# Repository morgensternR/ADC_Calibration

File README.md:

# ADC_Calibration
Collection/file history in making the ADC calibration board

 Copyright 2023 Ryan Morgenstern

   Licensed under the Apache License, Version 2.0 (the "License");
   you may not use this file except in compliance with the License.
   You may obtain a copy of the License at

       http://www.apache.org/licenses/LICENSE-2.0

   Unless required by applicable law or agreed to in writing, software
   distributed under the License is distributed on an "AS IS" BASIS,
   WITHOUT WARRANTIES OR CONDITIONS OF ANY KIND, either express or implied.
   See the License for the specific language governing permissions and
   limitations under the License.

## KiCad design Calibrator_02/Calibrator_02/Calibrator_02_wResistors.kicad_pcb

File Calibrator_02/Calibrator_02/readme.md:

Copyright 2023 Ryan Morgenstern

   Licensed under the Apache License, Version 2.0 (the "License");
   you may not use this file except in compliance with the License.
   You may obtain a copy of the License at

       http://www.apache.org/licenses/LICENSE-2.0

   Unless required by applicable law or agreed to in writing, software
   distributed under the License is distributed on an "AS IS" BASIS,
   WITHOUT WARRANTIES OR CONDITIONS OF ANY KIND, either express or implied.
   See the License for the specific language governing permissions and
   limitations under the License.

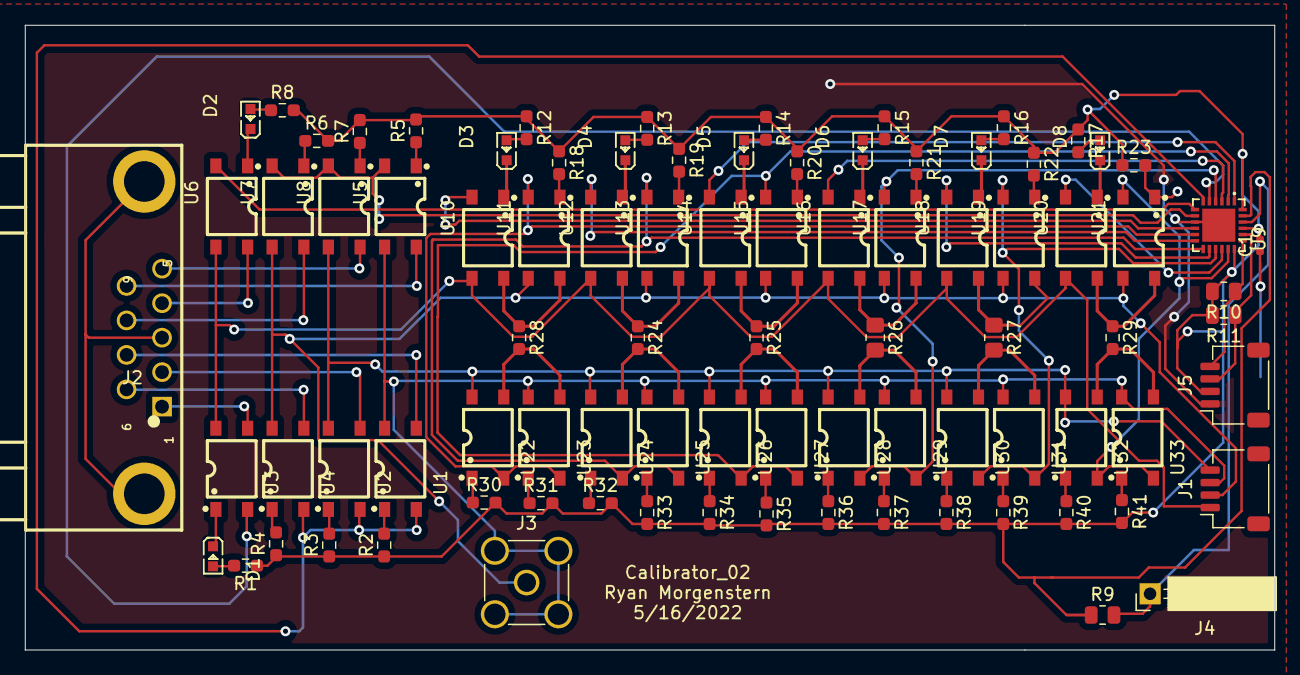
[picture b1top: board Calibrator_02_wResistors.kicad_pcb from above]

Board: 2 copper layers, 100.0 x 50.0 mm, 88 parts (0 on the bottom side), 86 nets.

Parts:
C1: 100nF; C_0402_1005Metric
D1, D2, D3, D4, D5, D6, D7, D8: LED; LED0603-RD
J1, J5: Conn_01x04; JST_SH_SM04B-SRSS-TB_1x04-1MP_P1.00mm_Horizontal
J2: DB9_Female_MountingHoles; DSUB-TH_DMR-9S
J3: Conn_Coaxial; SMA_Amphenol_901-144_Vertical
J4: Conn_01x01_Female; PinSocket_1x01_P2.54mm_Horizontal
R1, R8, R12, R13, R14, R15, R16, R17: 95.3 1%; R_0603_1608Metric_Pad0.98x0.95mm_HandSolder
R2, R3, R4, R5, R6, R7, R18, R19, R20, R21, R22, R23, R30, R31, R32, R33, R34, R35, R36, R37, R38, R39, R40, R41: 84.5 1%; R_0603_1608Metric_Pad0.98x0.95mm_HandSolder
R9, R10, R11: 4.7K; R_0805_2012Metric
R24: 120K_0.1%; R_0603_1608Metric_Pad0.98x0.95mm_HandSolder
R25: 140K_0.1%; R_0603_1608Metric_Pad0.98x0.95mm_HandSolder
R26: 160K_0.1%; R_0805_2012Metric_Pad1.20x1.40mm_HandSolder
R27: 180K_0.1%; R_0805_2012Metric_Pad1.20x1.40mm_HandSolder
R28: 100K_0.1%; R_0603_1608Metric_Pad0.98x0.95mm_HandSolder
R29: 200K_0.1%; R_0603_1608Metric_Pad0.98x0.95mm_HandSolder
U1, U2, U3, U4, U5, U6, U7, U8, U10, U11, U12, U13, U14, U15, U16, U17, U18, U19, U20, U21, U22, U23, U24, U25, U26, U27, U28, U29, U30, U31, U32, U33: KAQY214STLD; SOP-4_L3.9-W4.4-P2.54-LS7.0-BR
U9: AW9523BTQR; TQFN-24_L4.0-W4.0-P0.50-TL-EP

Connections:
+3V3: C1.2, J5.2, R1.1, R2.1, R3.1, R4.1, R5.2, R6.2, R7.2, R8.2, R9.1, R10.2, R11.2, R12.1, R13.1, R14.1, R15.1, R16.1, R17.1, R18.1, R19.1, R20.1, R21.1, R22.1, R23.1, R30.2, R31.2, R32.2, R33.2, R34.2, R35.2, R36.2, R37.2, R38.2, R39.2, R40.2, R41.2, U9.18, U9.21, U9.23, U9.24
/I+: J2.1, U3.3
/I-: J2.2, U2.3
/I_00: U3.2, U9.5
/I_01: U1.2, U2.2, U4.2, U9.6
/I_02: U6.2, U9.7
/I_2+: J2.4, U6.4
/I_2-: J2.5, U8.4
/I_03: U5.2, U7.2, U8.2, U9.8
/I_04: U9.10, U10.2
/I_05: U9.11, U11.2, U22.2, U23.2
/I_06: U9.12, U12.2
/I_07: U9.13, U13.2, U24.2, U25.2
/I_10: U9.1, U14.2
/I_11: U9.2, U15.2, U26.2, U27.2
/I_12: U9.3, U16.2
/I_13: U9.4, U17.2, U28.2, U29.2
/I_14: U9.14, U18.2
/I_15: U9.15, U19.2, U30.2, U31.2
/I_16: U9.16, U20.2
/I_17: U9.17, U21.2, U32.2, U33.2
/Resistor_Network/I+: J1.1, U3.4, U6.3, U10.3, U12.3, U14.3, U16.3, U18.3, U20.3
/Resistor_Network/I-: J1.4, U2.4, U8.3, U22.4, U24.4, U26.4, U28.4, U30.4, U32.4
/Resistor_Network/V+: J1.2, J3.1, U4.4, U7.3, U11.3, U13.3, U15.3, U17.3, U19.3, U21.3
/Resistor_Network/V-: J1.3, J3.2, U1.4, U5.3, U23.4, U25.4, U27.4, U29.4, U31.4, U33.4
/V+: J2.6, U4.3
/V-: J2.7, U1.3
/V_2+: J2.8, U7.4
/V_2-: J2.9, U5.4
GND: C1.1, J5.1, U9.9, U9.25
GNDS: J2.0, J2.3
unnamed: D1.1, U3.1
unnamed: D1.2, R1.2
unnamed: D2.1, U6.1
unnamed: D2.2, R8.1
unnamed: D3.1, U10.1
unnamed: D3.2, R12.2
unnamed: D4.1, U12.1
unnamed: D4.2, R13.2
unnamed: D5.1, U14.1
unnamed: D5.2, R14.2
unnamed: D6.1, U16.1
unnamed: D6.2, R15.2
unnamed: D7.1, U18.1
unnamed: D7.2, R16.2
unnamed: D8.1, U20.1
unnamed: D8.2, R17.2
unnamed: J4.1, R9.2, U9.22
unnamed: J5.3, R11.1, U9.20
unnamed: J5.4, R10.1, U9.19
unnamed: R2.2, U1.1
unnamed: R3.2, U2.1
unnamed: R4.2, U4.1
unnamed: R5.1, U5.1
unnamed: R6.1, U7.1
unnamed: R7.1, U8.1
unnamed: R18.2, U11.1
unnamed: R19.2, U13.1
unnamed: R20.2, U15.1
unnamed: R21.2, U17.1
unnamed: R22.2, U19.1
unnamed: R23.2, U21.1
unnamed: R24.1, U12.4, U13.4
unnamed: R24.2, U24.3, U25.3
unnamed: R25.1, U14.4, U15.4
unnamed: R25.2, U26.3, U27.3
unnamed: R26.1, U16.4, U17.4
unnamed: R26.2, U28.3, U29.3
unnamed: R27.1, U18.4, U19.4
unnamed: R27.2, U30.3, U31.3
unnamed: R28.1, U10.4, U11.4
unnamed: R28.2, U22.3, U23.3
unnamed: R29.1, U20.4, U21.4
unnamed: R29.2, U32.3, U33.3
unnamed: R30.1, U22.1
unnamed: R31.1, U23.1
unnamed: R32.1, U24.1
unnamed: R33.1, U25.1
unnamed: R34.1, U26.1
unnamed: R35.1, U27.1
unnamed: R36.1, U28.1
unnamed: R37.1, U29.1
unnamed: R38.1, U30.1
unnamed: R39.1, U31.1
unnamed: R40.1, U32.1
unnamed: R41.1, U33.1

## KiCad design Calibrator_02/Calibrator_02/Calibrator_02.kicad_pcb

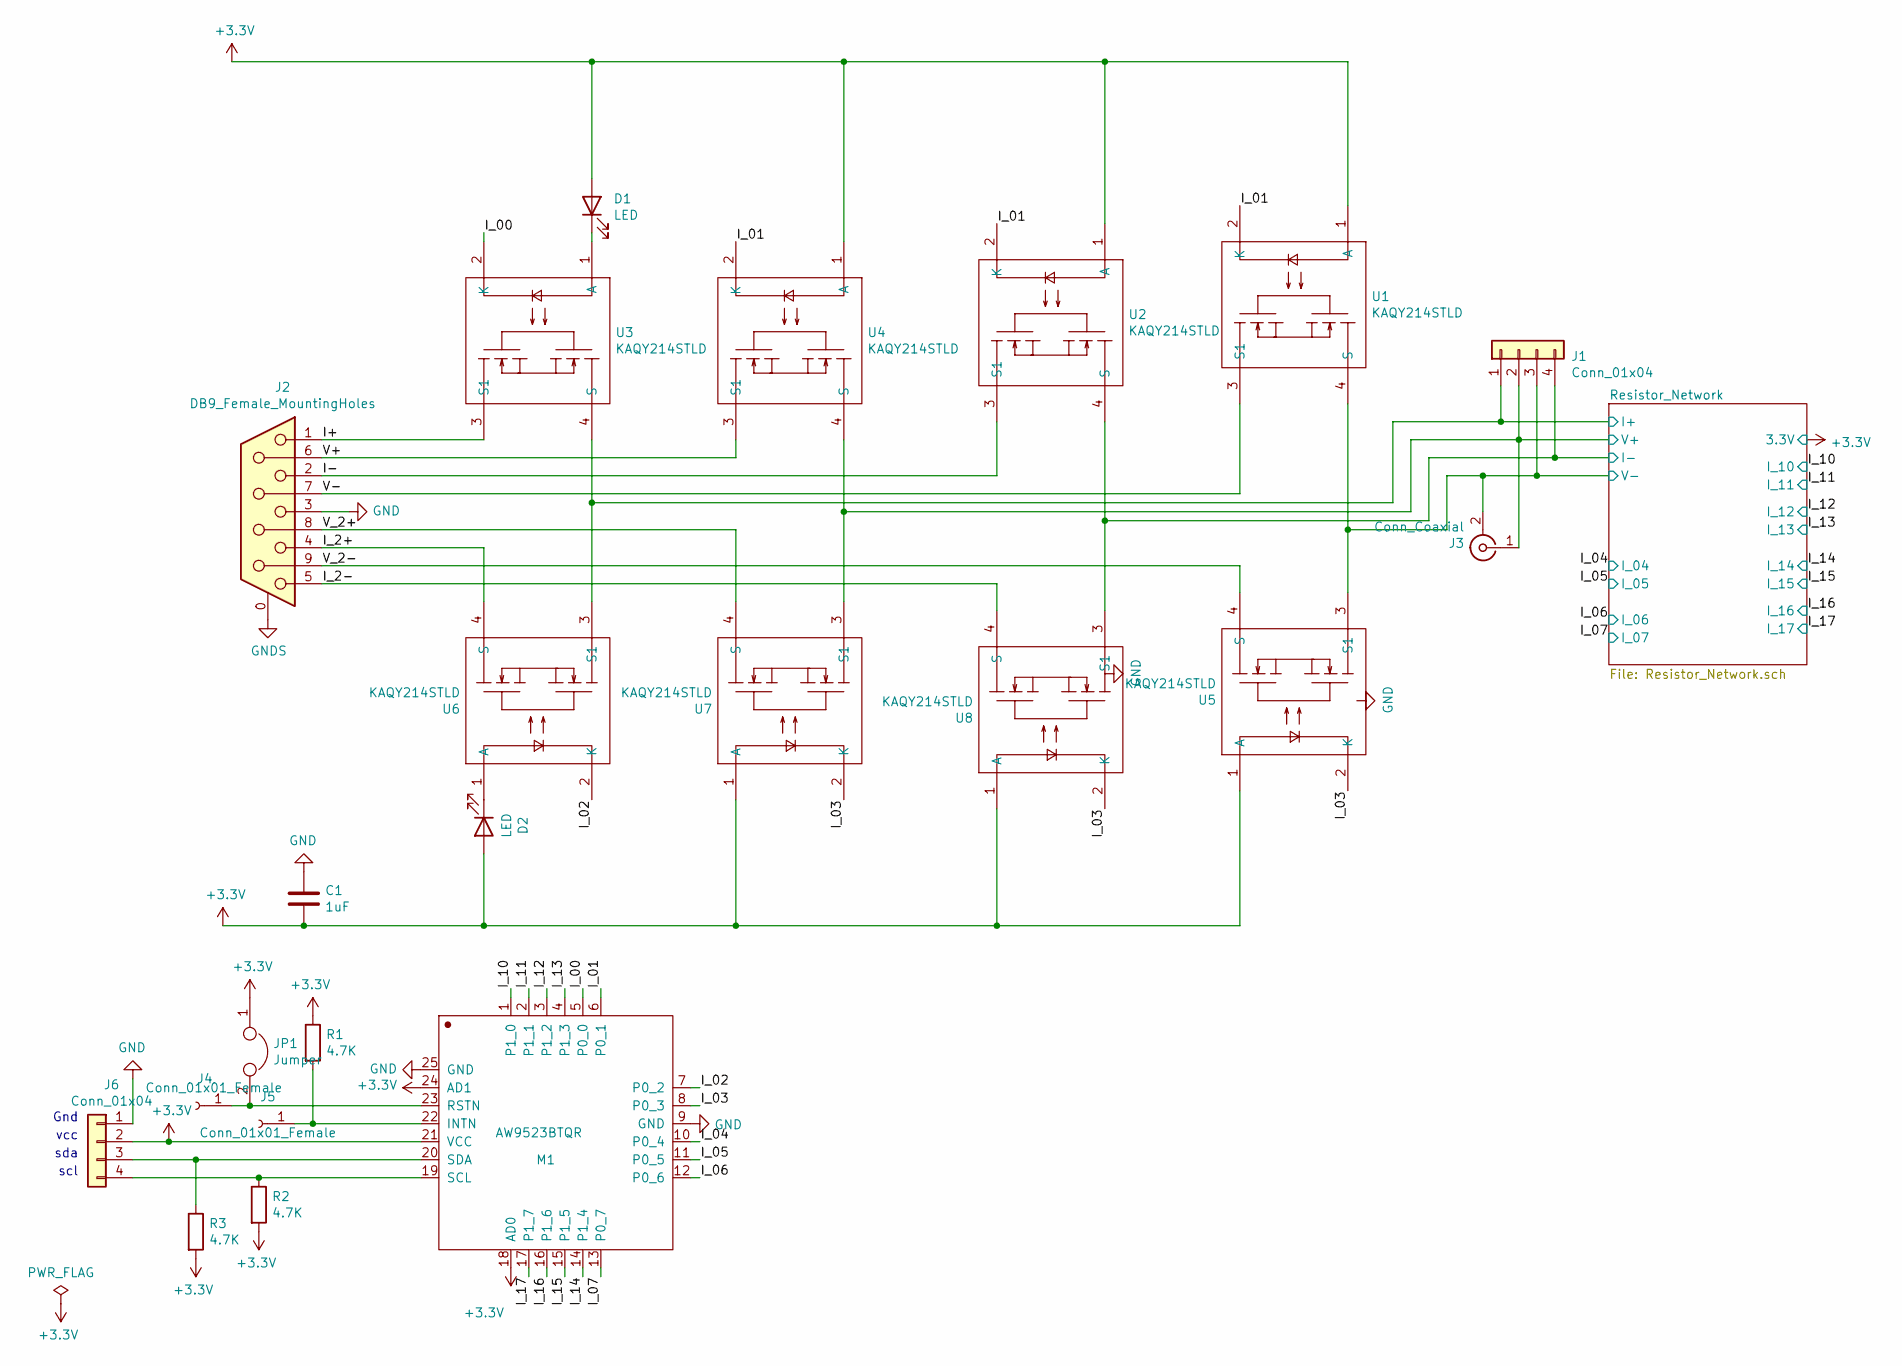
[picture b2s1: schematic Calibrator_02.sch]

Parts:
C1: 1uF; C_0402_1005Metric; LCSC C77009
D1, D2: LED; LED0603-RD; LCSC C125093
J1, J6: Conn_01x04; JST_SH_SM04B-SRSS-TB_1x04-1MP_P1.00mm_Horizontal; LCSC C371571
J2: DB9_Female_MountingHoles; DSUB-TH_DMR-9S; LCSC C141882
J3: Conn_Coaxial; SMA_Amphenol_901-144_Vertical
J4, J5: Conn_01x01_Female; PinSocket_1x01_P2.54mm_Horizontal
JP1: Jumper; SolderJumper-2_P1.3mm_Open_RoundedPad1.0x1.5mm
M1: AW9523BTQR; TQFN-24_L4.0-W4.0-P0.50-TL-EP; LCSC C148077
R1, R2, R3: 4.7K; R_0805_2012Metric; LCSC C17673
U1, U2, U3, U4, U5, U6, U7, U8: KAQY214STLD; SOP-4_L3.9-W4.4-P2.54-LS7.0-BR; LCSC C113331

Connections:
/I+: J2.1, U3.3 (S1)
/I-: J2.2, U2.3 (S1)
/I_00: M1.5 (P0_0), U3.2 (K)
/I_01: M1.6 (P0_1), U1.2 (K), U2.2 (K), U4.2 (K)
/I_02: M1.7 (P0_2), U6.2 (K)
/I_2+: J2.4, U6.4 (S)
/I_2-: J2.5, U8.4 (S)
/I_03: M1.8 (P0_3), U5.2 (K), U7.2 (K), U8.2 (K)
/I_04: M1.10 (P0_4); also elsewhere on the board
/I_05: M1.11 (P0_5); also elsewhere on the board
/I_06: M1.12 (P0_6); also elsewhere on the board
/I_07: M1.13 (P0_7); also elsewhere on the board
/I_10: M1.1 (P1_0); also elsewhere on the board
/I_11: M1.2 (P1_1); also elsewhere on the board
/I_12: M1.3 (P1_2); also elsewhere on the board
/I_13: M1.4 (P1_3); also elsewhere on the board
/I_14: M1.14 (P1_4); also elsewhere on the board
/I_15: M1.15 (P1_5); also elsewhere on the board
/I_16: M1.16 (P1_6); also elsewhere on the board
/I_17: M1.17 (P1_7); also elsewhere on the board
/Resistor_Network/I+: J1.1, U3.4 (S), U6.3 (S1); also elsewhere on the board
/Resistor_Network/I-: J1.4, U2.4 (S), U8.3 (S1); also elsewhere on the board
/Resistor_Network/V+: J1.2, J3.1 (In), U4.4 (S), U7.3 (S1); also elsewhere on the board
/Resistor_Network/V-: J1.3, J3.2 (Ext), U1.4 (S), U5.3 (S1); also elsewhere on the board
/V+: J2.6, U4.3 (S1)
/V-: J2.7, U1.3 (S1)
/V_2+: J2.8, U7.4 (S)
/V_2-: J2.9, U5.4 (S)
GND: C1.1, J2.3, J6.1, M1.9 (GND), M1.25 (GND)
GNDS: J2.0 (PAD)
unnamed: D1.1 (K), U3.1 (A)
unnamed: D2.1 (K), U6.1 (A)
unnamed: J5.1, M1.22 (INTN), R1.2
unnamed: J6.3, M1.20 (SDA), R3.1
unnamed: J6.4, M1.19 (SCL), R2.1

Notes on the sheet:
Gnd
vcc
sda
scl

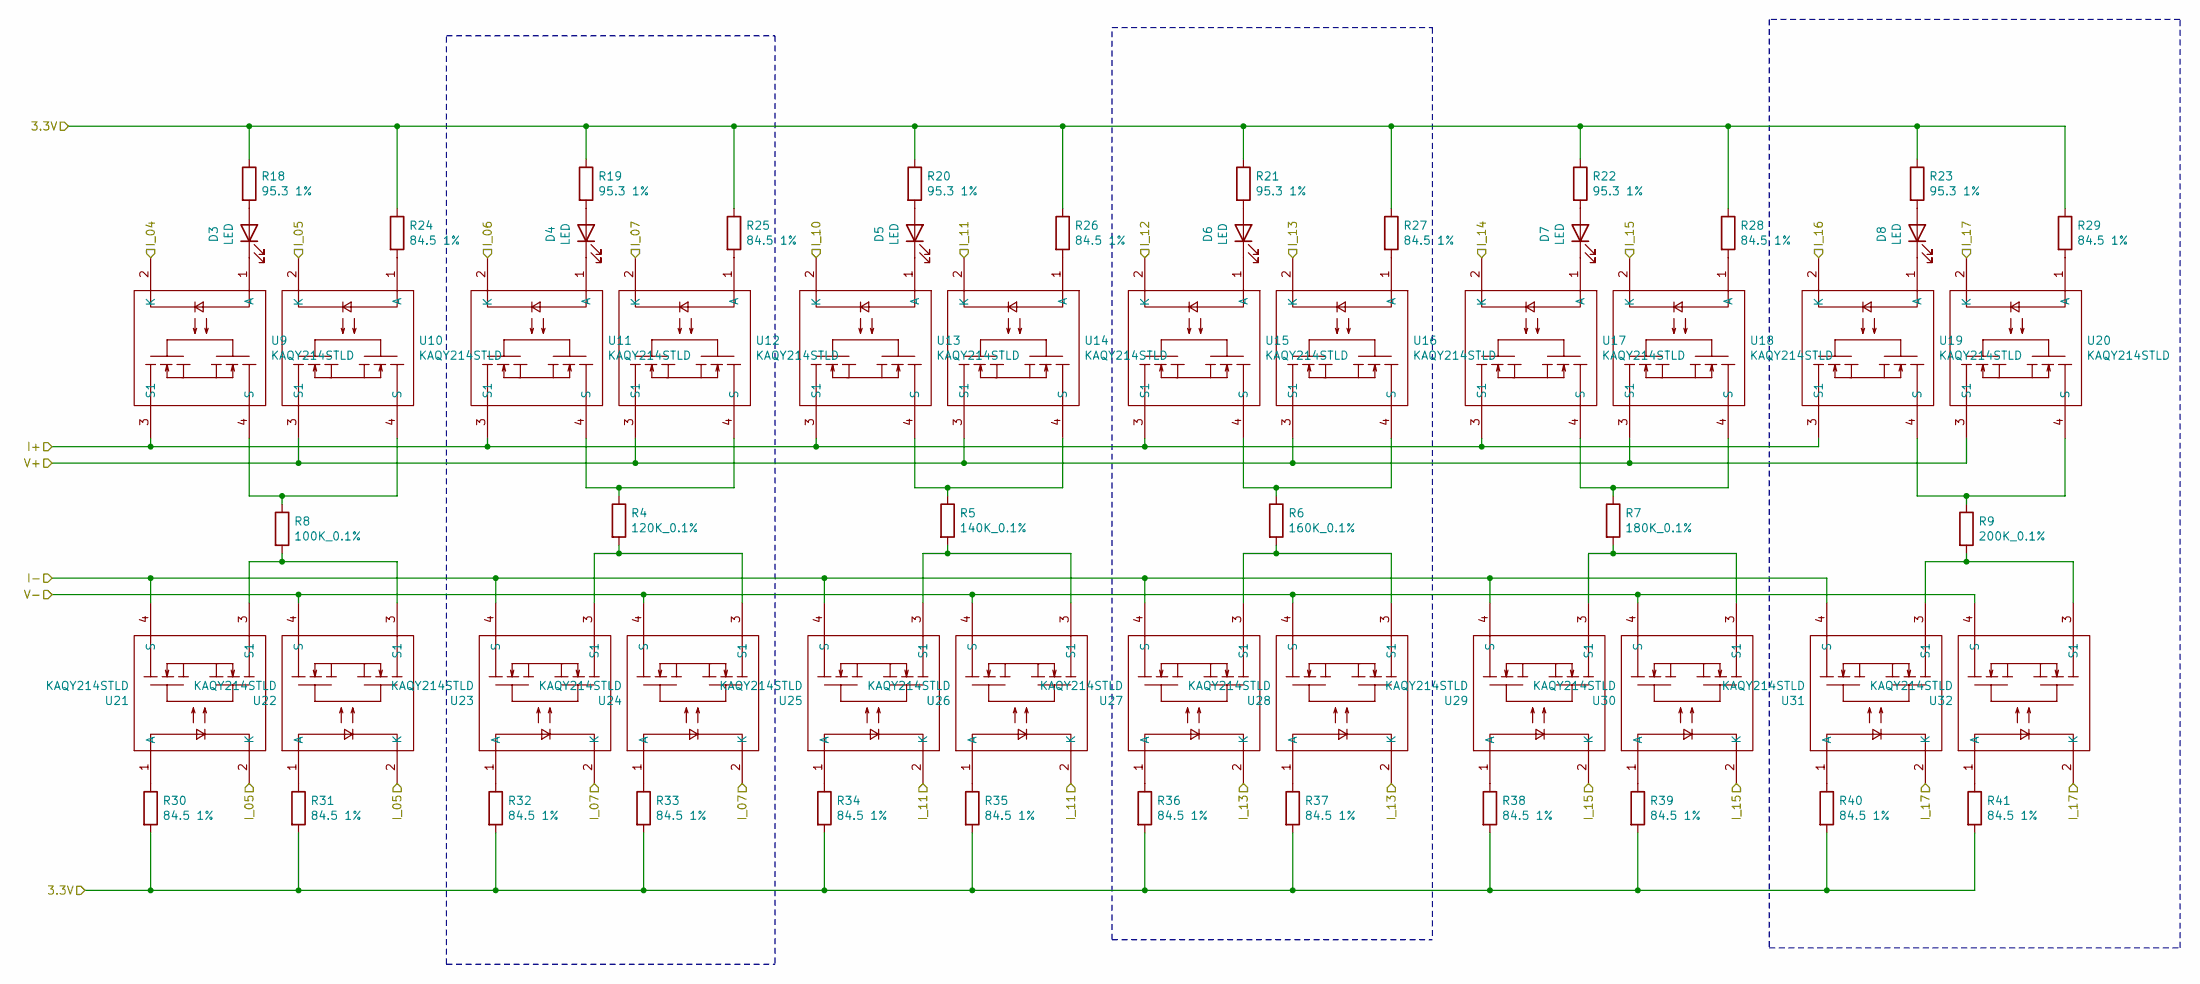
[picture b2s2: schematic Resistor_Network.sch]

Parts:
D3, D4, D5, D6, D7, D8: LED; LED0603-RD; LCSC C125093
R4: 120K_0.1%; R_0603_1608Metric_Pad0.98x0.95mm_HandSolder; LCSC C136959
R5: 140K_0.1%; R_0603_1608Metric_Pad0.98x0.95mm_HandSolder; LCSC C326761
R6: 160K_0.1%; R_0805_2012Metric_Pad1.20x1.40mm_HandSolder; LCSC C473318
R7: 180K_0.1%; R_0805_2012Metric_Pad1.20x1.40mm_HandSolder; LCSC C473319
R8: 100K_0.1%; R_0603_1608Metric_Pad0.98x0.95mm_HandSolder; LCSC C335088
R9: 200K_0.1%; R_0603_1608Metric_Pad0.98x0.95mm_HandSolder; LCSC C394540
R18, R19, R20, R21, R22, R23: 95.3 1%; R_0603_1608Metric_Pad0.98x0.95mm_HandSolder; LCSC C218188
R24, R25, R26, R27, R28, R29, R30, R31, R32, R33, R34, R35, R36, R37, R38, R39, R40, R41: 84.5 1%; R_0603_1608Metric_Pad0.98x0.95mm_HandSolder; LCSC C177824
U9, U10, U11, U12, U13, U14, U15, U16, U17, U18, U19, U20, U21, U22, U23, U24, U25, U26, U27, U28, U29, U30, U31, U32: KAQY214STLD; SOP-4_L3.9-W4.4-P2.54-LS7.0-BR; LCSC C113331

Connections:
/I_04: U9.2 (K); also elsewhere on the board
/I_05: U10.2 (K), U21.2 (K), U22.2 (K); also elsewhere on the board
/I_06: U11.2 (K); also elsewhere on the board
/I_07: U12.2 (K), U23.2 (K), U24.2 (K); also elsewhere on the board
/I_10: U13.2 (K); also elsewhere on the board
/I_11: U14.2 (K), U25.2 (K), U26.2 (K); also elsewhere on the board
/I_12: U15.2 (K); also elsewhere on the board
/I_13: U16.2 (K), U27.2 (K), U28.2 (K); also elsewhere on the board
/I_14: U17.2 (K); also elsewhere on the board
/I_15: U18.2 (K), U29.2 (K), U30.2 (K); also elsewhere on the board
/I_16: U19.2 (K); also elsewhere on the board
/I_17: U20.2 (K), U31.2 (K), U32.2 (K); also elsewhere on the board
/Resistor_Network/I+: U9.3 (S1), U11.3 (S1), U13.3 (S1), U15.3 (S1), U17.3 (S1), U19.3 (S1); also elsewhere on the board
/Resistor_Network/I-: U21.4 (S), U23.4 (S), U25.4 (S), U27.4 (S), U29.4 (S), U31.4 (S); also elsewhere on the board
/Resistor_Network/V+: U10.3 (S1), U12.3 (S1), U14.3 (S1), U16.3 (S1), U18.3 (S1), U20.3 (S1); also elsewhere on the board
/Resistor_Network/V-: U22.4 (S), U24.4 (S), U26.4 (S), U28.4 (S), U30.4 (S), U32.4 (S); also elsewhere on the board
unnamed: D3.1 (K), U9.1 (A)
unnamed: D3.2 (A), R18.2
unnamed: D4.1 (K), U11.1 (A)
unnamed: D4.2 (A), R19.2
unnamed: D5.1 (K), U13.1 (A)
unnamed: D5.2 (A), R20.2
unnamed: D6.1 (K), U15.1 (A)
unnamed: D6.2 (A), R21.2
unnamed: D7.1 (K), U17.1 (A)
unnamed: D7.2 (A), R22.2
unnamed: D8.1 (K), U19.1 (A)
unnamed: D8.2 (A), R23.2
unnamed: R4.1, U11.4 (S), U12.4 (S)
unnamed: R4.2, U23.3 (S1), U24.3 (S1)
unnamed: R5.1, U13.4 (S), U14.4 (S)
unnamed: R5.2, U25.3 (S1), U26.3 (S1)
unnamed: R6.1, U15.4 (S), U16.4 (S)
unnamed: R6.2, U27.3 (S1), U28.3 (S1)
unnamed: R7.1, U17.4 (S), U18.4 (S)
unnamed: R7.2, U29.3 (S1), U30.3 (S1)
unnamed: R8.1, U9.4 (S), U10.4 (S)
unnamed: R8.2, U21.3 (S1), U22.3 (S1)
unnamed: R9.1, U19.4 (S), U20.4 (S)
unnamed: R9.2, U31.3 (S1), U32.3 (S1)
unnamed: R24.2, U10.1 (A)
unnamed: R25.2, U12.1 (A)
unnamed: R26.2, U14.1 (A)
unnamed: R27.2, U16.1 (A)
unnamed: R28.2, U18.1 (A)
unnamed: R29.2, U20.1 (A)
unnamed: R30.1, U21.1 (A)
unnamed: R31.1, U22.1 (A)
unnamed: R32.1, U23.1 (A)
unnamed: R33.1, U24.1 (A)
unnamed: R34.1, U25.1 (A)
unnamed: R35.1, U26.1 (A)
unnamed: R36.1, U27.1 (A)
unnamed: R37.1, U28.1 (A)
unnamed: R38.1, U29.1 (A)
unnamed: R39.1, U30.1 (A)
unnamed: R40.1, U31.1 (A)
unnamed: R41.1, U32.1 (A)

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
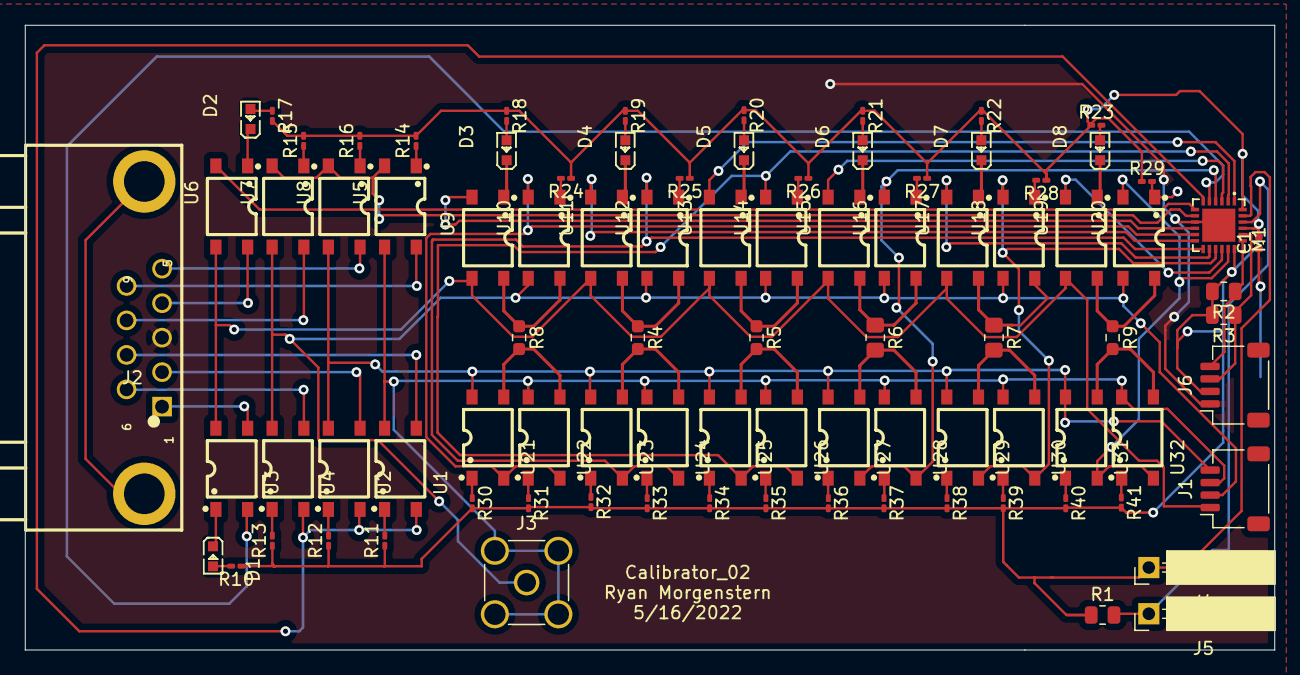
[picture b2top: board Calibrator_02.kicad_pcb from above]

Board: 2 copper layers, 100.0 x 50.0 mm, 89 parts (0 on the bottom side), 85 nets.

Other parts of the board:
R10, R17: 95.3 1%; R_0201_0603Metric_Pad0.64x0.40mm_HandSolder
R11, R12, R13, R14, R15, R16: 84.5 1%; R_0201_0603Metric_Pad0.64x0.40mm_HandSolder

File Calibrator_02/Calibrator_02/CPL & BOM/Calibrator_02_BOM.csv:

Comment,Designator,Footprint,LCSC
"1uF","C1","Capacitor_SMD:C_0402_1005Metric","C77009"
"LED","D1,D2,D3,D4,D5,D6,D7,D8","0_Resistor_02:LED0603-RD","C125093"
"Conn_01x04","J1,J6","Connector_JST:JST_SH_SM04B-SRSS-TB_1x04-1MP_P1.00mm_Horizontal","C371571"
"DB9_Female_MountingHoles","J2","0_Resistor_02:DSUB-TH_DMR-9S","C141882"
"Conn_Coaxial","J3","Connector_Coaxial:SMA_Amphenol_901-144_Vertical",""
"Conn_01x01_Female","J5","Connector_PinSocket_2.54mm:PinSocket_1x01_P2.54mm_Horizontal",""
"Jumper","JP1","Jumper:SolderJumper-2_P1.3mm_Open_RoundedPad1.0x1.5mm",""
"AW9523BTQR","M1","0_Resistor_02:TQFN-24_L4.0-W4.0-P0.50-TL-EP","C148077"
"4.7K","R1,R2,R3","Resistor_SMD:R_0805_2012Metric","C17673"
"95.3 1%","R10,R17,R18,R19,R20,R21,R22,R23","Resistor_SMD:R_0201_0603Metric_Pad0.64x0.40mm_HandSolder","C218188"
"84.5 1%","R11,R12,R13,R14,R15,R16,R24,R25,R26,R27,R28,R29,R30,R31,R32,R33,R34,R35,R36,R37,R38,R39,R40,R41","Resistor_SMD:R_0201_0603Metric_Pad0.64x0.40mm_HandSolder","C177824"
"120K_0.1%","R4","Resistor_SMD:R_0603_1608Metric_Pad0.98x0.95mm_HandSolder","C136959"
"140K_0.1%","R5","Resistor_SMD:R_0603_1608Metric_Pad0.98x0.95mm_HandSolder","C326761"
"160K_0.1%","R6","Resistor_SMD:R_0805_2012Metric_Pad1.20x1.40mm_HandSolder","C473318"
"180K_0.1%","R7","Resistor_SMD:R_0805_2012Metric_Pad1.20x1.40mm_HandSolder","C473319"
"100K_0.1%","R8","Resistor_SMD:R_0603_1608Metric_Pad0.98x0.95mm_HandSolder","C335088"
"200K_0.1%","R9","Resistor_SMD:R_0603_1608Metric_Pad0.98x0.95mm_HandSolder","C394540"
"KAQY214STLD","U1,U2,U3,U4,U5,U6,U7,U8,U9,U10,U11,U12,U13,U14,U15,U16,U17,U18,U19,U20,U21,U22,U23,U24,U25,U26,U27,U28,U29,U30,U31,U32","0_Resistor_02:SOP-4_L3.9-W4.4-P2.54-LS7.0-BR","C113331"

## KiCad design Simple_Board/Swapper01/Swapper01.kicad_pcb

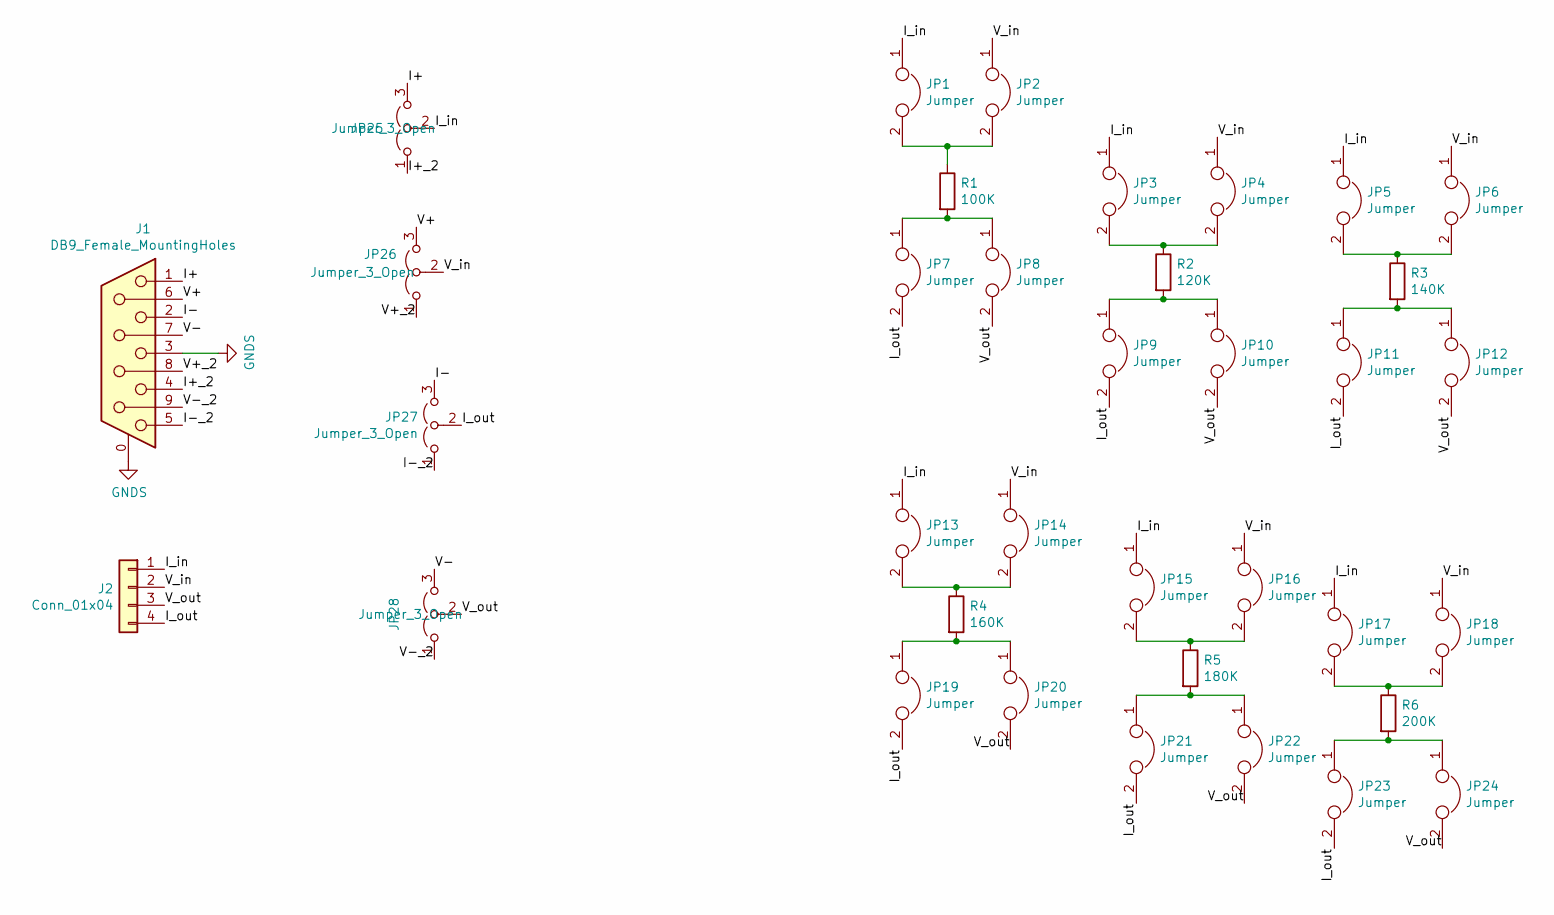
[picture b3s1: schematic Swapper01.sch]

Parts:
J1: DB9_Female_MountingHoles; DSUB-TH_DMR-9S; LCSC C141882
J2: Conn_01x04; JST_SH_SM04B-SRSS-TB_1x04-1MP_P1.00mm_Horizontal
JP1, JP2, JP3, JP4, JP5, JP6, JP7, JP8, JP9, JP10, JP11, JP12, JP13, JP14, JP15, JP16, JP17, JP18, JP19, JP20, JP21, JP22, JP23, JP24: Jumper; SolderJumper-2_P1.3mm_Open_RoundedPad1.0x1.5mm
JP25, JP26, JP27, JP28: Jumper_3_Open; SolderJumper-3_P1.3mm_Open_Pad1.0x1.5mm
R1: 100K; R_0603_1608Metric_Pad0.98x0.95mm_HandSolder; LCSC C335088
R2: 120K; R_0603_1608Metric_Pad0.98x0.95mm_HandSolder; LCSC C136959
R3: 140K; R_0603_1608Metric_Pad0.98x0.95mm_HandSolder; LCSC C326761
R4: 160K; R_0805_2012Metric_Pad1.20x1.40mm_HandSolder; LCSC C473318
R5: 180K; R_0805_2012Metric_Pad1.20x1.40mm_HandSolder; LCSC C473319
R6: 200K; R_0603_1608Metric_Pad0.98x0.95mm_HandSolder; LCSC C394540

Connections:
/I+: J1.1, JP25.3 (B)
/I+_2: J1.4, JP25.1 (A)
/I-: J1.2, JP27.3 (B)
/I-_2: J1.5, JP27.1 (A)
/I_in: J2.1, JP1.1, JP3.1, JP5.1, JP13.1, JP15.1, JP17.1, JP25.2 (C)
/I_out: J2.4, JP7.2, JP9.2, JP11.2, JP19.2, JP21.2, JP23.2, JP27.2 (C)
/V+: J1.6, JP26.3 (B)
/V+_2: J1.8, JP26.1 (A)
/V-: J1.7, JP28.3 (B)
/V-_2: J1.9, JP28.1 (A)
/V_in: J2.2, JP2.1, JP4.1, JP6.1, JP14.1, JP16.1, JP18.1, JP26.2 (C)
/V_out: J2.3, JP8.2, JP10.2, JP12.2, JP20.2, JP22.2, JP24.2, JP28.2 (C)
GNDS: J1.0 (PAD), J1.3
unnamed: JP1.2, JP2.2, R1.1
unnamed: JP3.2, JP4.2, R2.1
unnamed: JP5.2, JP6.2, R3.1
unnamed: JP7.1, JP8.1, R1.2
unnamed: JP9.1, JP10.1, R2.2
unnamed: JP11.1, JP12.1, R3.2
unnamed: JP13.2, JP14.2, R4.1
unnamed: JP15.2, JP16.2, R5.1
unnamed: JP17.2, JP18.2, R6.1
unnamed: JP19.1, JP20.1, R4.2
unnamed: JP21.1, JP22.1, R5.2
unnamed: JP23.1, JP24.1, R6.2

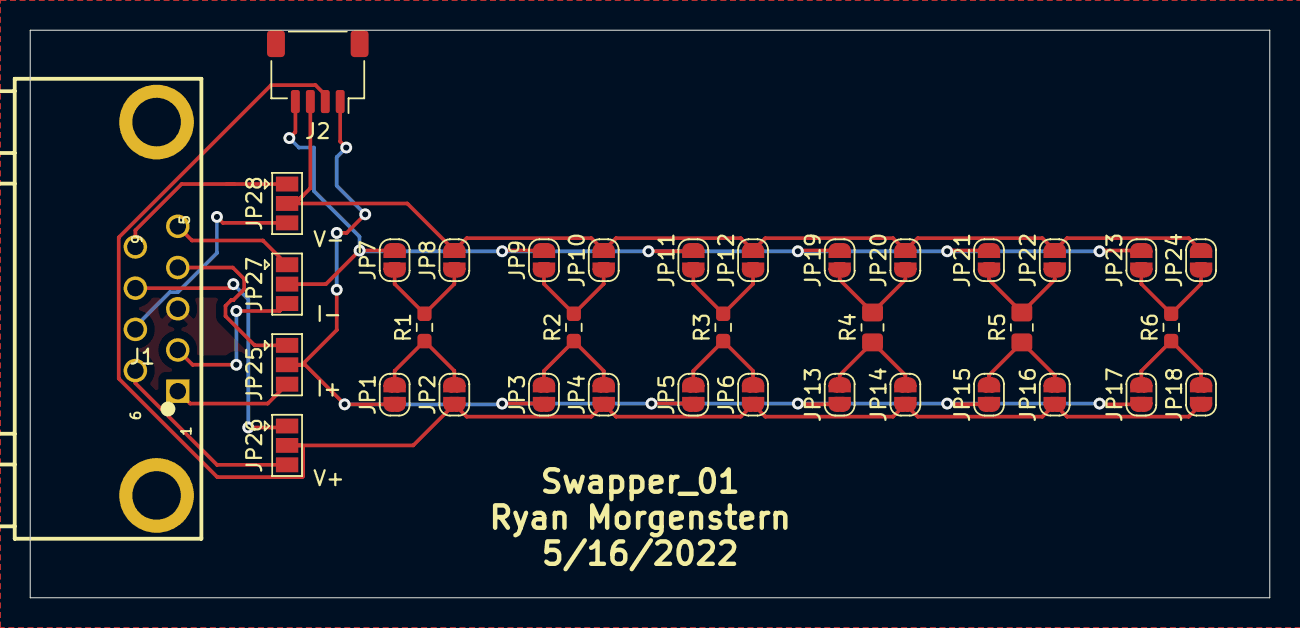
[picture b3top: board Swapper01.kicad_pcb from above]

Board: 2 copper layers, 83.0 x 38.0 mm, 36 parts (0 on the bottom side), 24 nets.

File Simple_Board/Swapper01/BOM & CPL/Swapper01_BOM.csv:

Comment,Designator,Footprint,LCSC
"DB9_Female_MountingHoles","J1","0_Swapper01:DSUB-TH_DMR-9S","C141882"
"Conn_01x04","J2","Connector_JST:JST_SH_SM04B-SRSS-TB_1x04-1MP_P1.00mm_Horizontal",""
"Jumper","JP1,JP2,JP3,JP4,JP5,JP6,JP7,JP8,JP9,JP10,JP11,JP12,JP13,JP14,JP15,JP16,JP17,JP18,JP19,JP20,JP21,JP22,JP23,JP24","Jumper:SolderJumper-2_P1.3mm_Open_RoundedPad1.0x1.5mm",""
"Jumper_3_Open","JP25,JP26,JP27,JP28","Jumper:SolderJumper-3_P1.3mm_Open_Pad1.0x1.5mm",""
"100K","R1","Resistor_SMD:R_0603_1608Metric_Pad0.98x0.95mm_HandSolder","C335088"
"120K","R2","Resistor_SMD:R_0603_1608Metric_Pad0.98x0.95mm_HandSolder","C136959"
"140K","R3","Resistor_SMD:R_0603_1608Metric_Pad0.98x0.95mm_HandSolder","C326761"
"160K","R4","Resistor_SMD:R_0805_2012Metric_Pad1.20x1.40mm_HandSolder","C473318"
"180K","R5","Resistor_SMD:R_0805_2012Metric_Pad1.20x1.40mm_HandSolder","C473319"
"200K","R6","Resistor_SMD:R_0603_1608Metric_Pad0.98x0.95mm_HandSolder","C394540"
